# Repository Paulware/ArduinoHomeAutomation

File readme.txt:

View the HomeAutomation.docx file for detailed information on setup.

Arduino sketches are located in the sketches directory
  The server directory has a the webserver sketch.
  The deviceClient has an example client sketch

Eagle schematics are located for enc28J60 DIY Arduino PCBs.
In the schematics directory
   1) EtherWeeny is a standard pcb for standard 10 pin ENC28J60.  A 3.3 V voltage regulator is added.
   2) EtherWeeny2 is a pcb for the less standard 12 pin ENC28J60.  This device has its own 3.3V regulator built in.

Web-Pages that can be run on an ipad or laptop are located in the webPages directory.
   1) tank.htm is an example that can be used to drive a tank.  A specific matching client sketch is not yet
      available for this tank.htm   
   
Future schematics and sketches will be added for X-10 control.

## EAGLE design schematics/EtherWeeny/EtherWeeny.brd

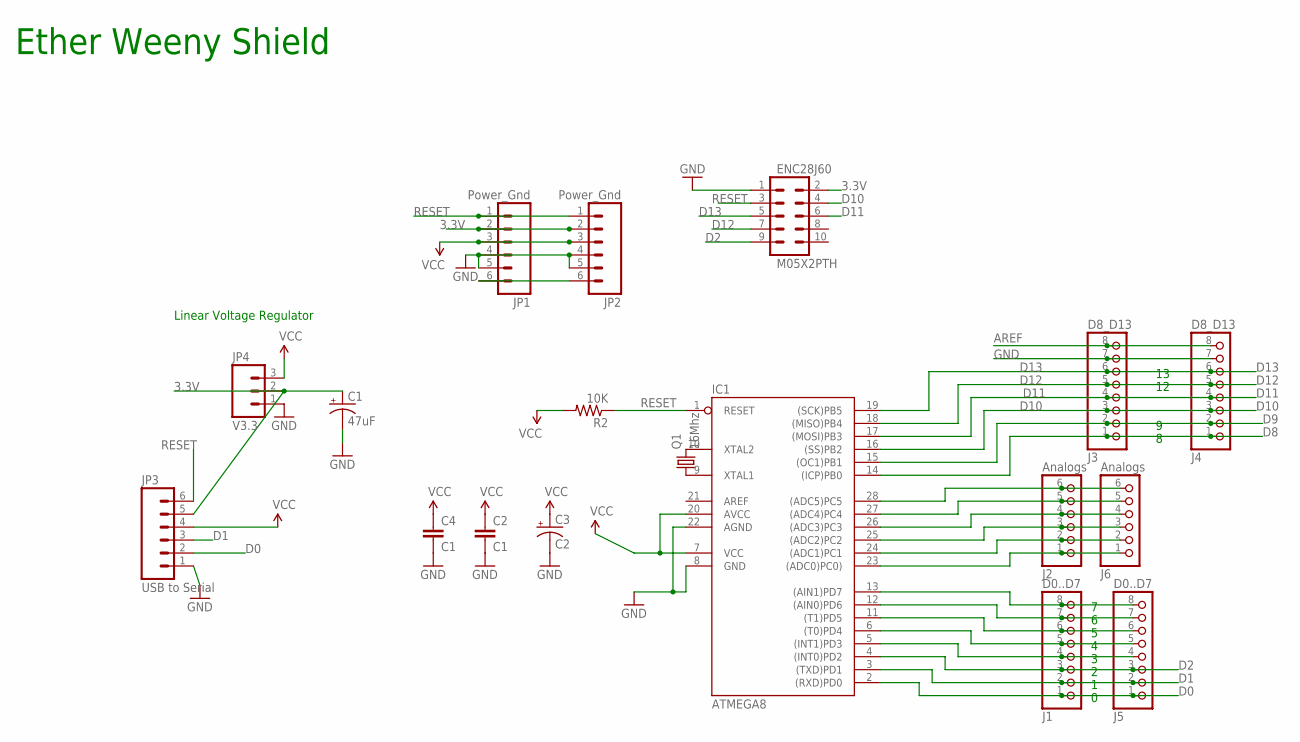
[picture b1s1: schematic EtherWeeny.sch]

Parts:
C1: 47uF; CPOL-RADIAL-100UF-25V
C2, C4: C1; CAP-PTH-SMALL
C3: C2; CPOL-RADIAL-100UF-25V
ENC28J60: M05X2PTH; AVR_ICSP
IC1: ATMEGA8; DIL28-3
J1, J5: D0..D7; 1X08
J2, J6: Analogs; 1X06
J3, J4: D8_D13; 1X08
JP1, JP2: Power_Gnd; 1X06
JP3: USB to Serial; 1X06
JP4: V3.3; 1X03
Q1: 16Mhz; HC49US
R2: 10K; AXIAL-0.3

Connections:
3.3V: C1.1 (+), ENC28J60.2, JP1.2, JP2.2, JP3.5, JP4.2
AREF: IC1.21 (AREF), J3.8, J4.8
D0: IC1.2 ((RXD)PD0), J1.1, J5.1, JP3.2
D1: IC1.3 ((TXD)PD1), J1.2, J5.2, JP3.3
D2: ENC28J60.9, IC1.4 ((INT0)PD2), J1.3, J5.3
D8: IC1.14 ((ICP)PB0), J3.1, J4.1
D9: IC1.15 ((OC1)PB1), J3.2, J4.2
D10: ENC28J60.4, IC1.16 ((SS)PB2), J3.3, J4.3
D11: ENC28J60.6, IC1.17 ((MOSI)PB3), J3.4, J4.4
D12: ENC28J60.7, IC1.18 ((MISO)PB4), J3.5, J4.5
D13: ENC28J60.5, IC1.19 ((SCK)PB5), J3.6, J4.6
GND: C1.2 (-), C2.2, C3.2 (-), C4.2, ENC28J60.1, IC1.8 (GND), IC1.22 (AGND), J3.7, J4.7, JP1.4, JP1.5, JP2.4, JP2.5, JP3.1, JP4.1
unnamed: IC1.10 (XTAL2), Q1.2
unnamed: IC1.9 (XTAL1), Q1.1
unnamed: JP1.6, JP2.6
unnamed: IC1.5 ((INT1)PD3), J1.4, J5.4
unnamed: IC1.6 ((T0)PD4), J1.5, J5.5
unnamed: IC1.11 ((T1)PD5), J1.6, J5.6
unnamed: IC1.12 ((AIN0)PD6), J1.7, J5.7
unnamed: IC1.13 ((AIN1)PD7), J1.8, J5.8
unnamed: IC1.23 ((ADC0)PC0)), J2.1, J6.1
unnamed: IC1.24 ((ADC1)PC1), J2.2, J6.2
unnamed: IC1.25 ((ADC2)PC2), J2.3, J6.3
unnamed: IC1.26 ((ADC3)PC3), J2.4, J6.4
unnamed: IC1.27 ((ADC4)PC4), J2.5, J6.5
unnamed: IC1.28 ((ADC5)PC5), J2.6, J6.6
RESET: ENC28J60.3, IC1.1 (RESET), JP1.1, JP2.1, JP3.6, R2.P$1 (1)
VCC: C2.1, C3.1 (+), C4.1, IC1.7 (VCC), IC1.20 (AVCC), JP1.3, JP2.3, JP3.4, JP4.3, R2.P$2 (2)

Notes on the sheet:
Ether Weeny Shield
Linear Voltage Regulator

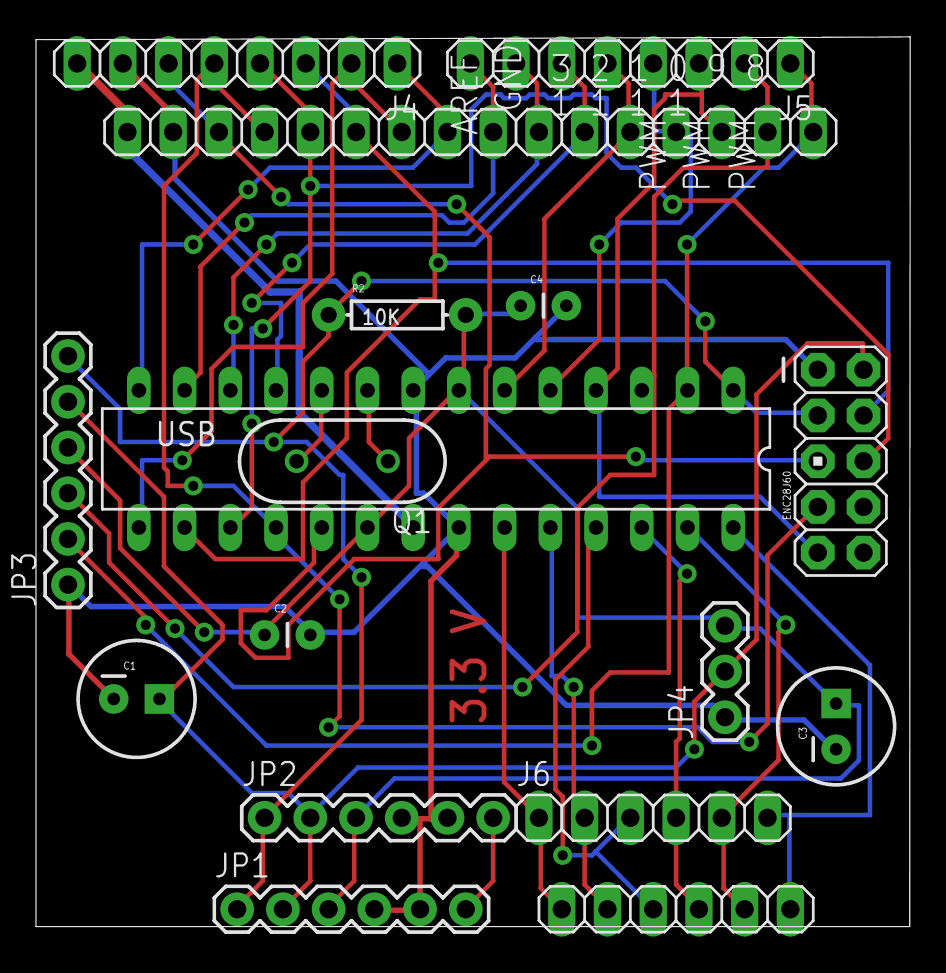
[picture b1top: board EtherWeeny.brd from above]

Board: 2 copper layers, 48.6 x 49.4 mm, 18 parts (0 on the bottom side), 28 nets.

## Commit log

2012-12-27 Initial Creation v.0.01 Prerelease
    Added documentation, sketches, schematics and web-pages
2012-12-27 v0.02 Prelease modified documentation
    Added HomeAutomation.docx detailed file
2012-12-27 V0.03
    Added power point documentation
